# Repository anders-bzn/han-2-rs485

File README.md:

# han-2-rs485
A small board that converts signal level from the HAN-port on swedish electricity power meter to RS-485. There is no connection for ground so a galvanically separated receiver is recommended. The board fits into a small ELKO standard connection box.

Created with KiCad 7.0 and [kicad-jlcpcb-tools](https://github.com/Bouni/kicad-jlcpcb-tools) plugin for creating fabrication files.

This is used together with a Raspberry Pi with a RS-485 HAT

## Software
Small python program for publishing MQTT data is located in the sw folder. It has one script that sets up the RPi and installs a service. The p1_sensors.yaml is a template for mapping sensors into Home Assistant. The content should be pasted into configuration.yaml in Home Assistant.

Change the han-mqtt-config.yaml with mqtt settings and report interval. Then install configuration and service by running:

    sudo ./han-mqtt.sh

## Acknowledgement
Acknowledgement to this github project: https://github.com/UdoK/esp8266_p1meter_sv from which I copied the mqtt topics.

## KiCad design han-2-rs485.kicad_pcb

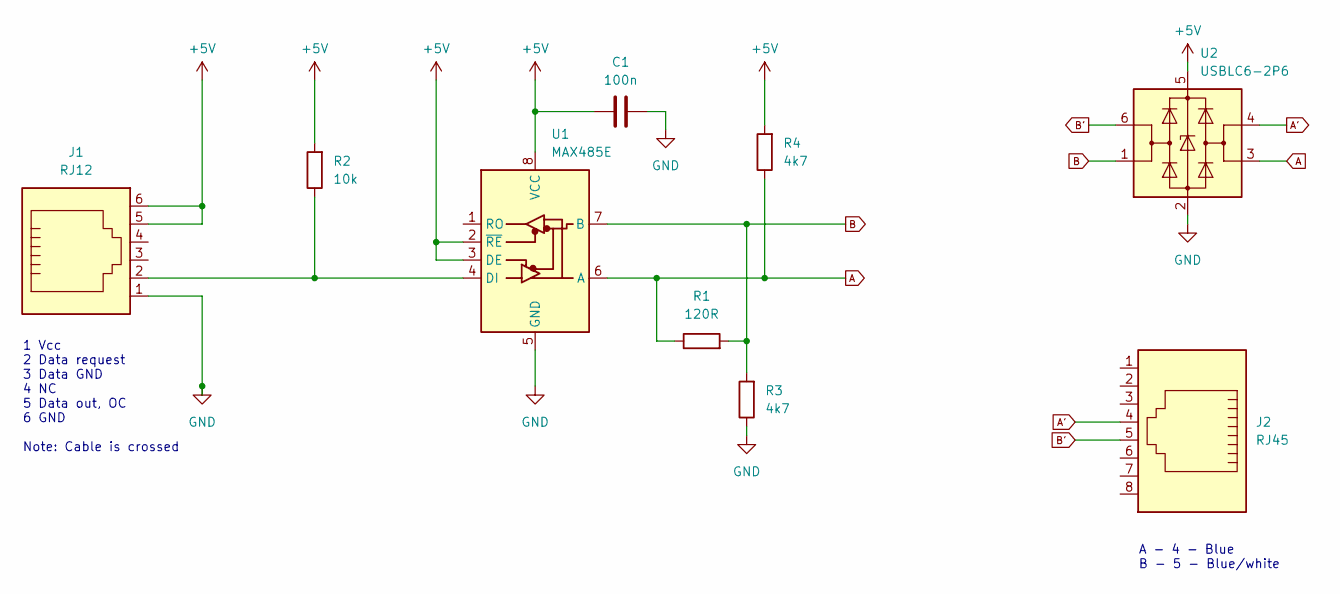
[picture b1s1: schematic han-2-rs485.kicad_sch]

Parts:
C1: 100n; C_0805_2012Metric_Pad1.18x1.45mm_HandSolder
J1: RJ12; RJ12_Amphenol_54601
J2: RJ45; RJ45_Amphenol_54602-x08_Horizontal
R1: 120R; R_0805_2012Metric
R2: 10k; R_0805_2012Metric
R3, R4: 4k7; R_0805_2012Metric
U1: MAX485E; SOIC-8_3.9x4.9mm_P1.27mm
U2: USBLC6-2P6; SOT-666

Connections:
+5V: C1.1, J1.5, J1.6, R2.2, R4.2, U1.2 (~RE), U1.3 (DE), U1.8 (VCC), U2.5 (VBUS)
A: R1.1, R4.1, U1.6 (A), U2.3 (I/O2)
A': J2.4, U2.4 (I/O2)
B: R1.2, R3.2, U1.7 (B), U2.1 (I/O1)
B': J2.5, U2.6 (I/O1)
GND: C1.2, J1.1, R3.1, U1.5 (GND), U2.2 (GND)
unnamed: J1.2, R2.1, U1.4 (DI)

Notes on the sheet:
1 Vcc 2 Data request 3 Data GND 4 NC 5 Data out, OC 6 GND Note: Cable is crossed
A - 4 - Blue B - 5 - Blue/white

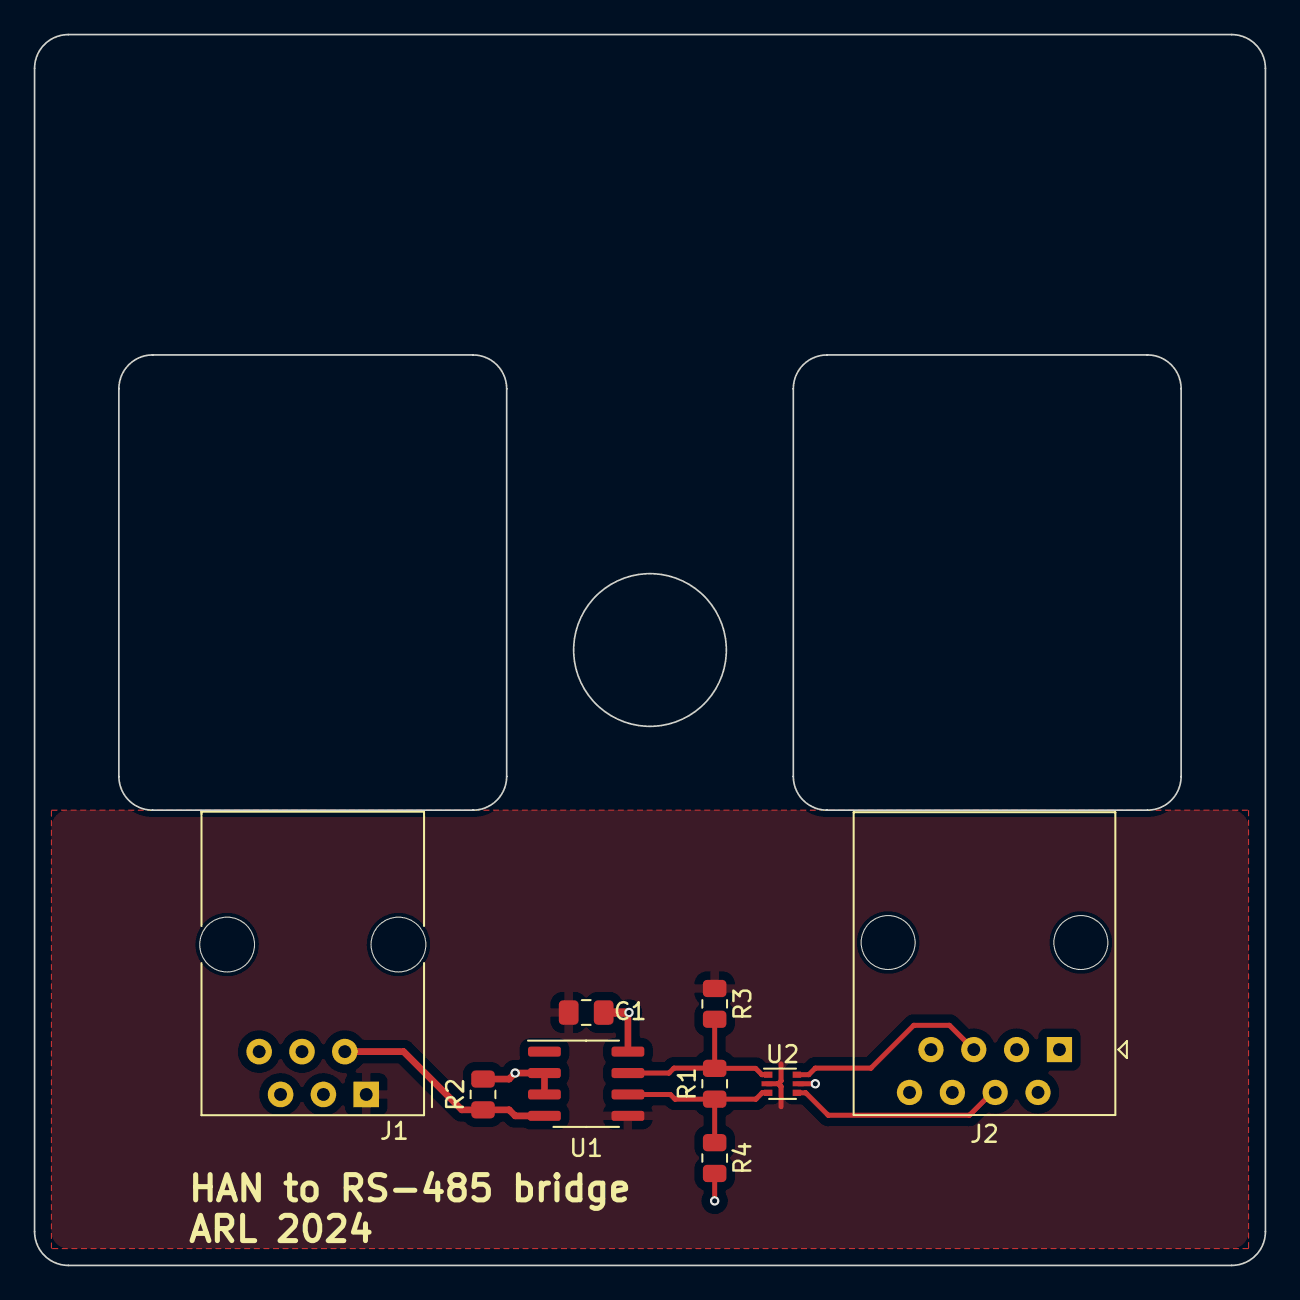
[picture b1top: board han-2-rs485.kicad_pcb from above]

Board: 2 copper layers, 73.0 x 73.0 mm, 9 parts (0 on the bottom side), 7 nets.

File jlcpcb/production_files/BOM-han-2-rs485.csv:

Comment,Designator,Footprint,LCSC
USBLC6-2P6,U2,SOT-666,
4k7,R4,R_0805_2012Metric,
4k7,R3,R_0805_2012Metric,
RJ12,J1,RJ12_Amphenol_54601,
RJ45,J2,RJ45_Amphenol_54602-x08_Horizontal,
MAX485E,U1,SOIC-8_3.9x4.9mm_P1.27mm,
10k,R2,R_0805_2012Metric,
100n,C1,C_0805_2012Metric_Pad1.18x1.45mm_HandSolder,
120R,R1,R_0805_2012Metric,

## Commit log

2024-05-02 Add files
2024-05-02 Add README.md
2024-05-02 Generated schematic pdf
2024-05-05 Add .gitignore
2025-01-07 Added python service for MQTT publish
2025-01-07 README.md updated
2025-01-18 sw: Devided each measurements into separate topic.
    Added a mapping template for Home Assistant. Updated README.md
2025-01-18 sw: Renamed instant_power_current to current
2025-01-21 sw: Make it configurable
2025-01-21 Use correct topic mapping
